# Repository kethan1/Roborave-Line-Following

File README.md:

# Roborave Line Follower

**Project Goal: Detect and followed a line using the picamera and dump balls into designated area.**

Links: \
http://www.roborave.org/linefollowing \
http://www.roborave.org/files/2019_Line_Following_Rules.pdf?v=1549335217 \
http://olivertrevor.tech/roborave

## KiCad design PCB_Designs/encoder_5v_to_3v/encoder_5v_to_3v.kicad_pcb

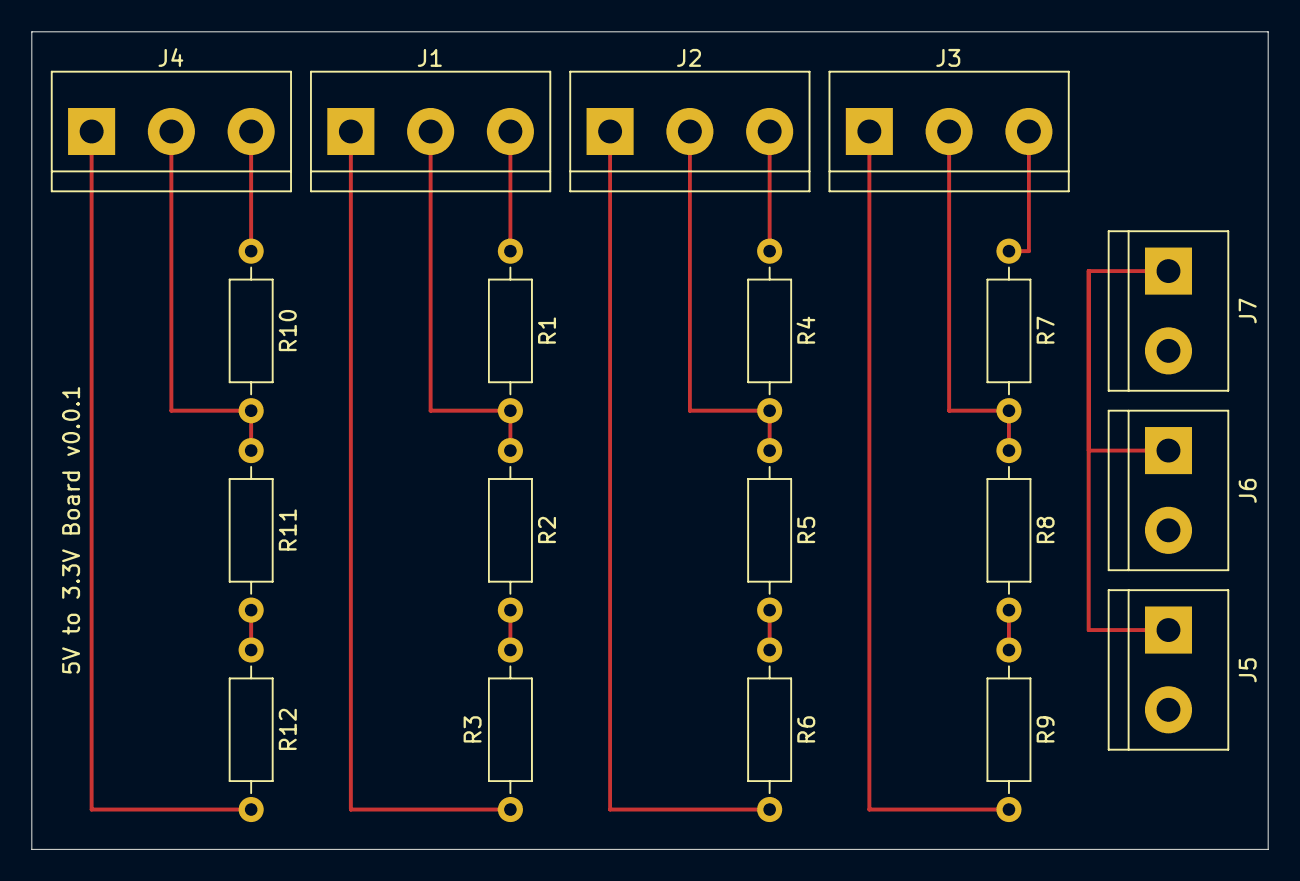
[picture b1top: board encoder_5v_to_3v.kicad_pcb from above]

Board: 2 copper layers, 78.7 x 52.1 mm, 19 parts (0 on the bottom side), 14 nets.

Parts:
J1, J2, J3, J4: Screw_Terminal_01x03; TerminalBlock_bornier-3_P5.08mm
J5, J6, J7: Screw_Terminal_01x02; TerminalBlock_bornier-2_P5.08mm
R1, R2, R3, R4, R5, R6, R7, R8, R9, R10, R11, R12: R; R_Axial_DIN0207_L6.3mm_D2.5mm_P10.16mm_Horizontal

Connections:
GND: J1.1, J2.1, J3.1, J4.1, J5.2, J6.2, J7.2, R3.1, R6.2, R9.2, R12.2
unnamed: J1.2, R1.2, R2.1
unnamed: J1.3, R1.1
unnamed: J2.2, R4.2, R5.1
unnamed: J2.3, R4.1
unnamed: J3.2, R7.2, R8.1
unnamed: J3.3, R7.1
unnamed: J4.2, R10.2, R11.1
unnamed: J4.3, R10.1
unnamed: J5.1, J6.1, J7.1
unnamed: R2.2, R3.2
unnamed: R5.2, R6.1
unnamed: R8.2, R9.1
unnamed: R11.2, R12.1

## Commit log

2021-04-17 first commit!
2021-04-17 update fix q not working when trying to terminate
2021-04-17 add picamera support
2021-04-17 add command-line options
2021-04-17 tweek threasholding values
2021-04-17 tweek threadholding values
2021-04-17 update add PID
2021-04-18 update robot_main.py and rename images to have better names
2021-04-18 fix file error
2021-04-18 make motors move depending on line
2021-04-18 fix wheel pins numbers
2021-04-18 fix error when equation output too high
2021-04-19 fix if conditions
2021-04-19 add debugging
2021-04-19 fix errors
2021-04-19 update threshholding values
2021-04-19 tweek thresholding values and fix equation
2021-04-19 fix direction of image
2021-04-19 fix error
2021-04-19 rotate image
2021-04-19 try to fix erros
2021-04-19 fix more errors
2021-04-22 add testing
2021-04-22 remove folder
2021-04-22 update gitignore
2021-04-28 add config file and move PID class to seperate file
2021-05-02 update git repo
2021-05-08 add thunderborg testing
2021-05-18 update code
2021-05-26 add CPP encoder for speed
2021-06-04 maintain speed
2021-06-08 try ot make robot_main_thunderborg.py not spagetti code
2021-06-27 The starter workflow is broken!!
    https://github.com/actions/starter-workflows/issues/636
2021-06-28 add PID_CPP
2021-06-28 add changes
2021-06-28 new coommit
2021-06-28 clean up
2021-06-29 be big brain and fix the maintain_speed.py file!
2021-06-29 better function and variable names
2021-06-29 fix PID class
2021-06-29 update robot_main.py to control motors
2021-06-29 follow PEP8 better and remove unnecesary code
2021-06-29 fix variable undefined error in robot_main.py
2021-06-29 refactor robot_main_thunderborg.py
2021-06-29 fix up thunderborg testing
2021-06-29 Tweek the PID and encoder averaging in maintain_speed.py
2021-06-29 fix the CPP PID (even though we never needed it)
2021-06-29 remove unneeded import in robot_main.py
2021-06-29 make PEP 8 happy
2021-06-29 remove whitespace in ThunderBorg3.py
2021-06-29 disable printing if prod
2021-06-29 update robot_config.json values to oscilate
2021-06-30 fixed values
2021-07-01 fix the PID values
2021-07-02 fix code not working
2021-07-05 fix up code
2021-07-08 add 3d models
2021-07-08 fix up 3d models
2021-07-08 add intersection following
2021-07-09 add intersection
2021-07-12 fix the code lots of times
2021-07-12 baseline code
2021-07-12 fixed work!
2021-07-12 fix scad files
2021-07-13 fix up the code intersection
2021-07-14 move try except in opencv_line_detection.py
2021-07-14 remove unneeded code in opencv_line_detection.py
2021-07-15 Move to better image interpolation
    Moves to a better image interpolation (`INTER_CUBIC ` -> `INTER_AREA `).
    https://stackoverflow.com/a/51042104/13710015
2021-07-18 update 3d models for motors
2021-07-18 make a little better
2021-07-18 tweak interesection code and block printing when specifie
2021-07-18 add .pylintrc
2021-07-18 adding some stuff
2021-07-18 ignore picamera modules
2021-07-19 update dimensions
2021-07-19 openscad move to module
2021-07-19 add hall effect sensor
2021-07-21 add more
2021-07-27 modified motor mound files
2021-07-28 update 3d models
2021-07-28 fix dumb mistake about confusing diameter and radius
2021-07-28 add new branch
2021-07-28 update errors
2021-07-29 shorter code a little
2021-07-29 new commit
2021-07-29 update names
2021-07-29 fix thunderborg help function
2021-07-29 update Thunderborg library, fix comments at the top
2021-07-29 fix Thunderborg.py docstring indentation
2021-07-31 new commit!
2021-08-01 fix intersectiosn
2021-08-06 hardware test and chmod +x everything
2021-08-06 finishing up hardware test program
2021-08-07 new thunderborg addresses!
2021-08-08 add links
2021-08-09 Put links on new line
2021-08-09 add led turning on and oof
2021-08-09 add comment in code
2021-08-09 fix pep8 warnings a little
2021-08-10 update coede
2021-08-10 make program slightly better
2021-08-10 remove different controlling for different motors
2021-08-10 add stop.py
2021-08-16 switch to rgb led
2021-08-30 new code; updated for new robot
2021-09-04 new code
2021-09-05 fix tower code
2021-09-05 clean up code
2021-09-13 last
2021-09-13 rlock code
2021-10-03 ran black github action
2021-11-01 intersection turning
2021-11-09 add pcb design
2021-11-12 update pcb design
2021-12-27 update PCB
2022-01-04 more code!
2022-01-06 update the code and PID values
2022-10-01 sync code
